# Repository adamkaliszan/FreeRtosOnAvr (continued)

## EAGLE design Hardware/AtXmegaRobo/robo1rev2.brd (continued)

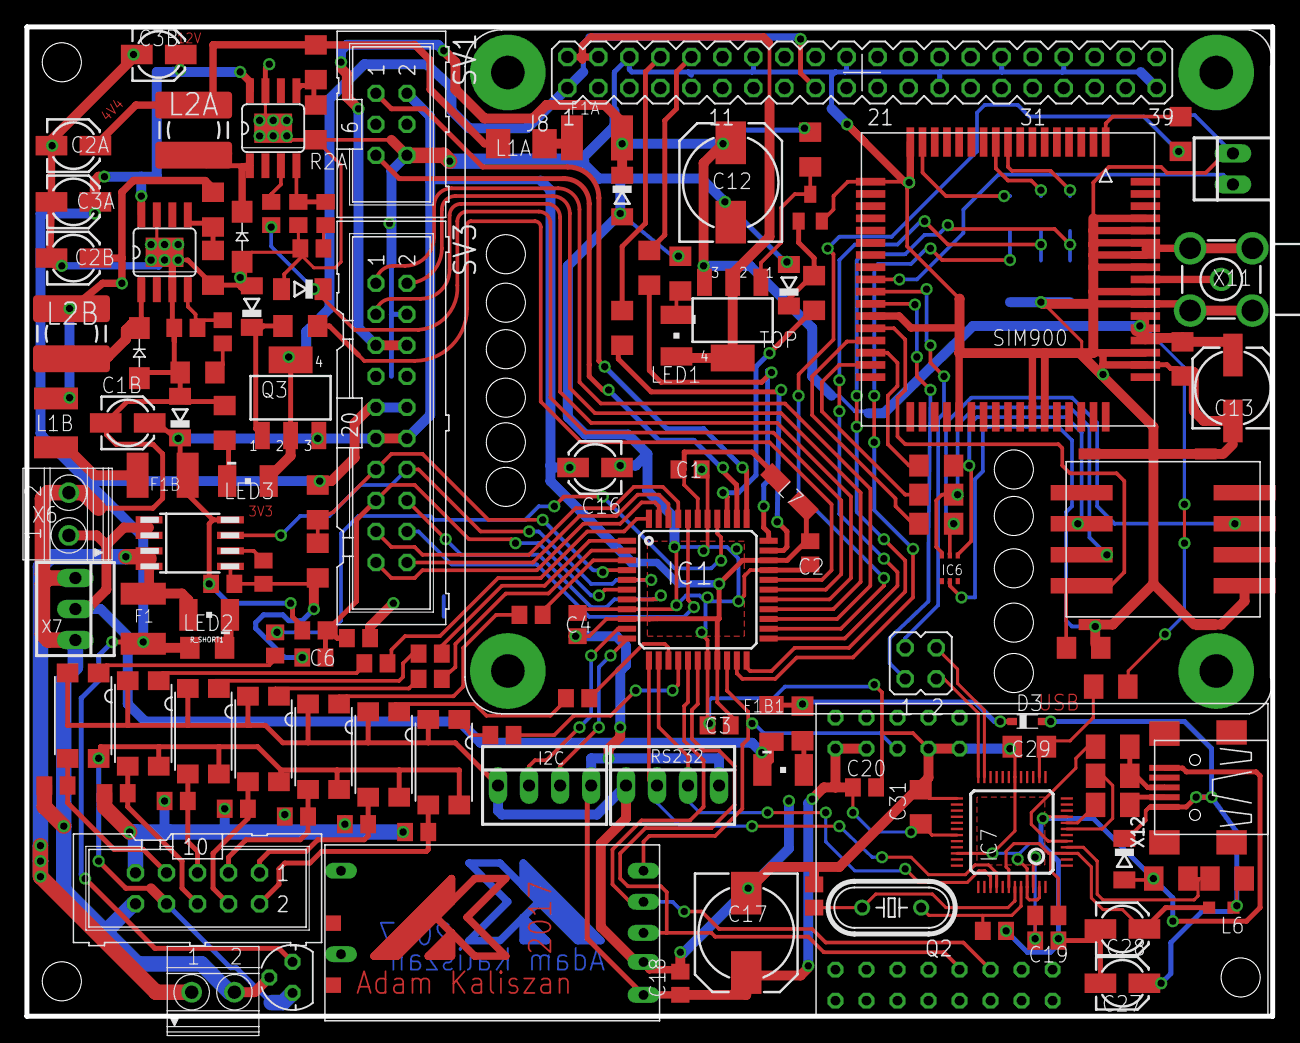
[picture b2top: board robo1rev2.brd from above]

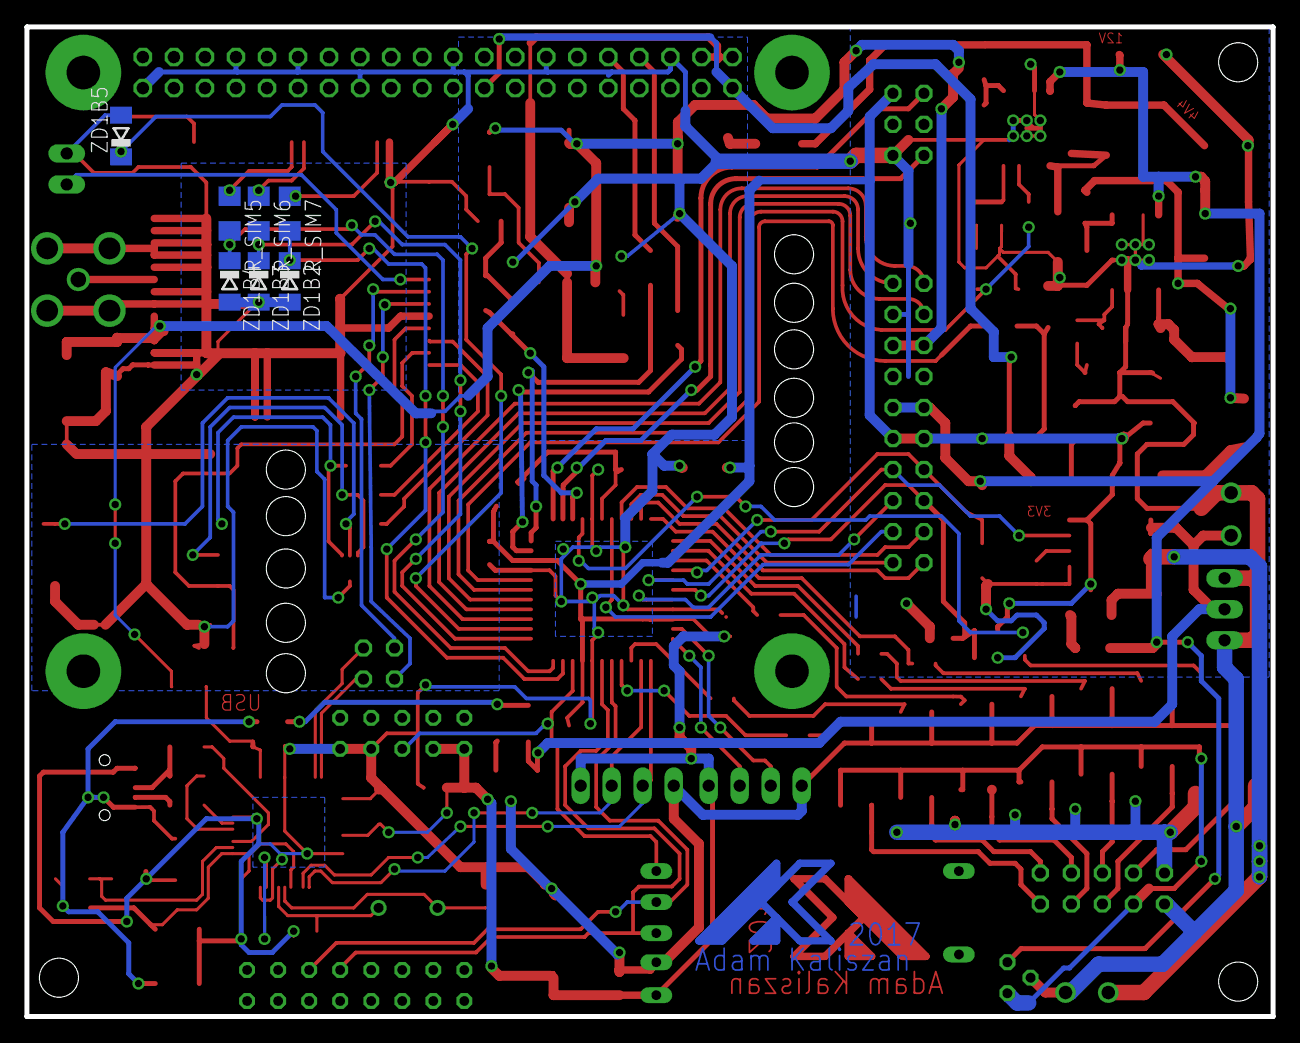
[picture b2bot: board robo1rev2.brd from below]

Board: 2 copper layers, 102.0 x 81.0 mm, 143 parts (8 on the bottom side), 113 nets.

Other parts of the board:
U$5, U$6: LOGO

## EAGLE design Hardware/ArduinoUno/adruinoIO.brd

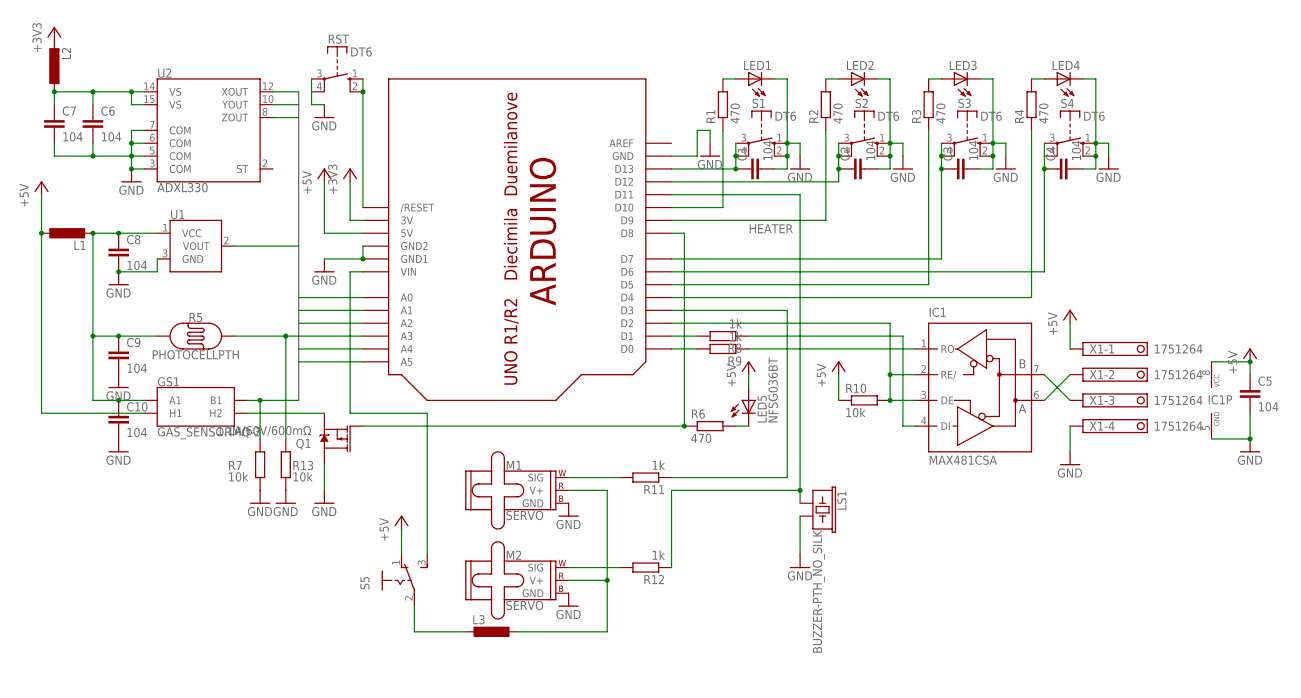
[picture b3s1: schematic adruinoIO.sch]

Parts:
C1, C2, C3, C4, C5, C6, C7, C8, C10: 104; C1206
C9: 104; C1206K
GS1: GAS_SENSORMQ-3; GAS_SENSOR
IC1: MAX481CSA; SO08
L1, L2, L3: L-EUL2012C; L2012C
LED1, LED2, LED3, LED4, LED5: NFSG036BT
LS1: BUZZER-PTH_NO_SILK; BUZZER-12MM-NS
M1, M2: SERVO; 1X03
Q1: 1.1A/60V/600mΩ; SOT23-3
R1, R2, R3, R4, R6: 470; R1206
R5: PHOTOCELLPTH; PHOTOCELL
R7, R10, R13: 10k; R1206
R8, R9, R11, R12: 1k; R1206
RST: DT6
S1, S2, S3, S4: DT6
S5: 255SB
U1: TMP36GT9; TO-92
U2: ADXL330; LFCSP-16-4X4
U$1: ARDUINO-NOHOLE
X1: 1751264

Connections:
5V_R: C8.1, C9.1, C10.1, GS1.A1, L1.2, R5.1, U1.1 (VCC)
+3V3: L2.2, U$1.3V
+5V: C5.1, GS1.HA (H1), IC1.8 (VCC), L1.1, LED5.A, R10.1, S5.1 (O), U$1.5V, X1.1
A0: R5.2, R13.1, U$1.A0
A1: U1.2 (VOUT), U$1.A1
A2: GS1.B1, R7.1, U$1.A2
A3: U2.8 (ZOUT), U$1.A3
A4: U2.10 (YOUT), U$1.A4
A5: U2.12 (XOUT), U$1.A5
BUZER: LS1.+ (1), R12.1, U$1.D11
GND: C1.2, C2.2, C3.2, C4.2, C5.2, C6.2, C7.2, C8.2, C9.2, C10.2, IC1.5 (GND), LED1.C, LED2.C, LED3.C, LED4.C, LS1.- (2), M1.3 (GND), M2.3 (GND), Q1.3 (D), R7.2, R13.2, RST.3, RST.4, S1.1 (S), S1.2 (S), S2.1 (S), S2.2 (S), S3.1 (S), S3.2 (S), S4.1 (S), S4.2 (S), U1.3 (GND), U2.3 (COM), U2.5 (COM), U2.6 (COM), U2.7 (COM), U$1.GND, U$1.GND1, U$1.GND2, X1.4
HEATER: Q1.1 (G), R6.1, U$1.D8
LED1: R1.1, U$1.D10
LED2: R2.1, U$1.D9
LED3: R3.1, U$1.D5
LED4: R4.1, U$1.D4
unnamed: L3.2, S5.2
unnamed: IC1.7 (B), X1.3
unnamed: IC1.6 (A), X1.2
unnamed: LED1.A, R1.2
unnamed: LED2.A, R2.2
unnamed: LED3.A, R3.2
unnamed: LED4.A, R4.2
unnamed: LED5.C, R6.2
unnamed: GS1.HB (H2), Q1.2 (S)
unnamed: M1.1 (SIG), R11.2
unnamed: M2.1 (SIG), R12.2
unnamed: C6.1, C7.1, L2.1, U2.14 (VS), U2.15 (VS)
RESET: RST.1 (S), RST.2 (S), U$1.RESET (/RESET)
RS485RX: IC1.1 (RO), R9.1
RS485_DE: IC1.2 (RE/), IC1.3 (DE), R10.2, U$1.D2
RS485_TX: IC1.4 (DI), R8.1
RX: R9.2, U$1.D0
SERVO1: R11.1, U$1.D3
SW1: C1.1, S1.3, S1.4, U$1.D13
SW2: C2.1, S2.3, S2.4, U$1.D12
SW3: C3.1, S3.3, S3.4, U$1.D7
SW4: C4.1, S4.3, S4.4, U$1.D6
TX: R8.2, U$1.D1
V_IN: S5.3 (S), U$1.VIN
V_SERVO: L3.1, M1.2 (V+), M2.2 (V+)

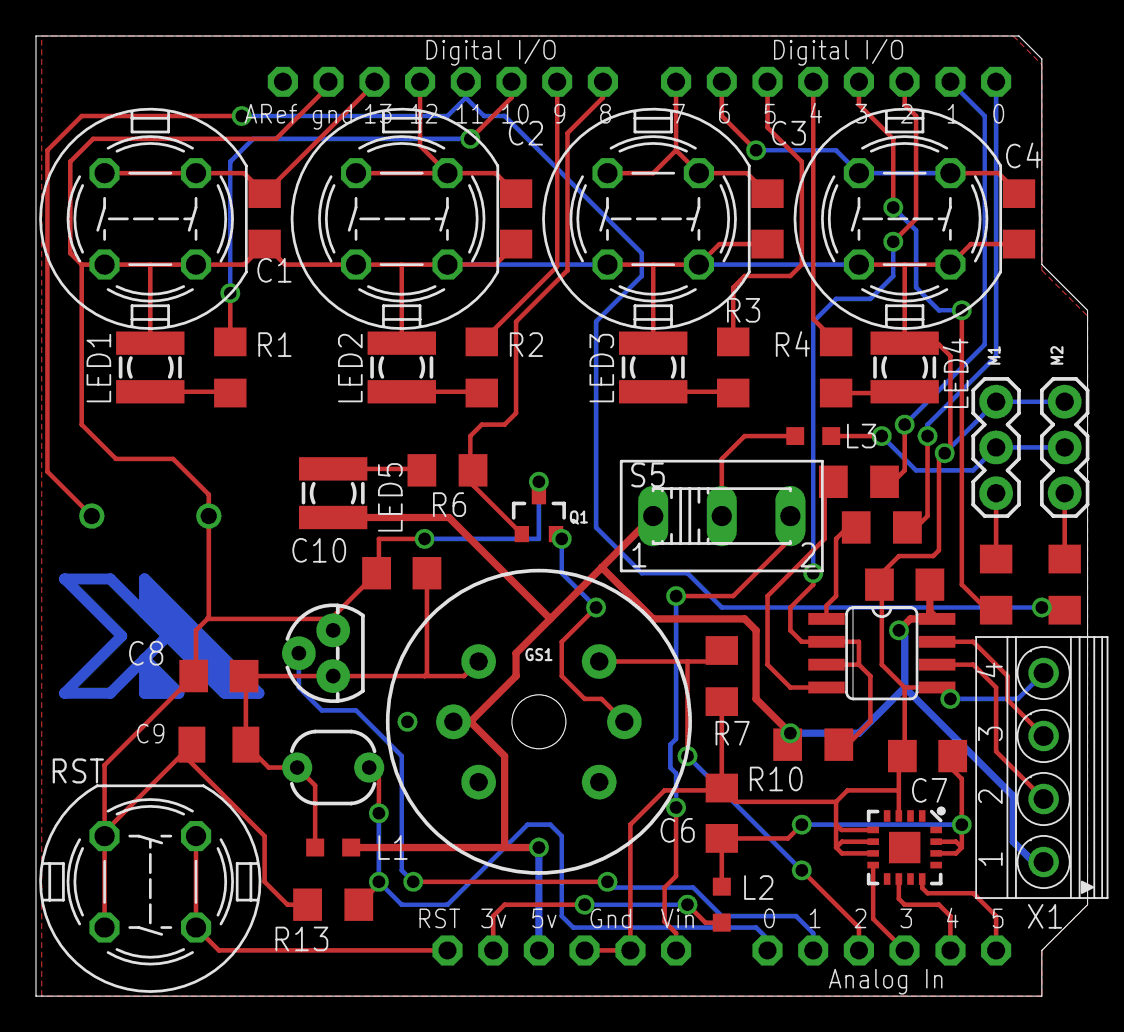
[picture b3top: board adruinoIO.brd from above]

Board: 2 copper layers, 58.4 x 53.3 mm, 48 parts (1 on the bottom side), 41 nets.

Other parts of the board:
U$2: LOGO

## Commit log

2018-01-04 Initial version
2018-01-04 Hardware schematics and PCB boards
2018-01-09 New subprojet DVR Controller
2018-01-11 DVR function for output controll
2018-01-18 AVR io helper for codeblocks
2018-01-18 atxmega helper
2018-01-20 ADC support
    Internal and power suply voltage mesarument.
    Current controll si not calibrated
2019-07-13 Migration to MPlab
2019-07-21 FTDI eeprom settings, avrdude upload scripts
2019-07-21 compuler custom: xc8 and avr-gcc
2019-09-17 Rover project
    Rover project has been converted to MPLAB ide
2019-09-17 Obsolete projects
2019-09-18 Rover Project CLI
    First working version of rower project
2019-09-22 Code refactorization
    Common libraries for xc8 and ave-gcc compiler
2019-09-22 I2C
    Initial files
2019-09-27 TWI in progress
2019-09-28 CLI can write and send TWI data
2019-09-29 new CLI
2019-09-29 preparing history
2019-10-02 CLI memory optimization
2019-10-11 CLI history in progress
2019-10-12 History is working. Some bugs in inserting
2019-10-13 CLI edit is working
2019-10-13 New memory optimized approach
2019-10-15 Preparing for ibus support
2019-10-16 RoverController hardware project imported from eagle
2019-10-19 Two variants of CLI history, version with non shared bufffers is working
2019-10-20 Some bug fixes for CLI history shared buffer
2019-10-20 Some bug fixes for CLI history shared buffer 2
2019-10-20 Twi fight
2020-05-03 I2c bugfix
2020-05-03 cleaning up conflicts
2020-05-03 Twi driver in progress
2020-05-09 TWI driver
2020-05-12 CLI optimization
2020-05-19 CLI history is working
2020-05-22 Command copletition by TAB key
2020-05-23 ADXL 345 is working
2020-05-24 Magnetometer support. Bugs wit float numbers stinn not solved
2020-05-26 Gcc cli bug fixes
2020-05-27 Barometer is working
2020-05-29 gyroscope module
2020-05-31 Gyro bug fixes
2020-05-31 twi driver optimization
2020-06-13 Rc ibus
2020-06-13 FreeRTOS core improvements
2020-06-14 Rc controll is working
2023-04-09 Initial cnanges nothing works
2023-04-09 Tixed include nightmre
